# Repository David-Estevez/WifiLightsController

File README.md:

WifiLightsController
------------------------

Control a strip of several WS2812B with an ubicuous ESP8266 module

Author: [DEF](https://github.com/David-Estevez)

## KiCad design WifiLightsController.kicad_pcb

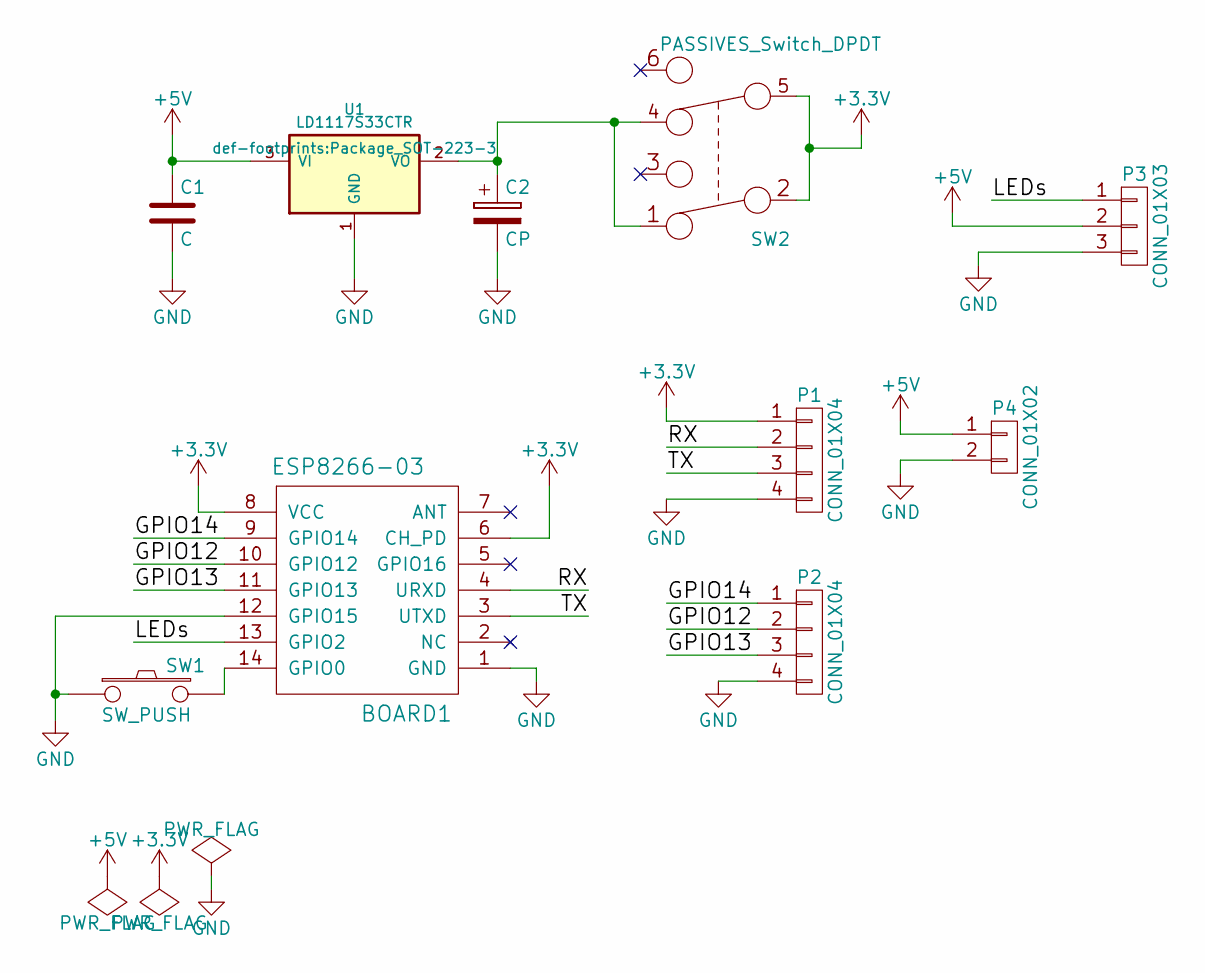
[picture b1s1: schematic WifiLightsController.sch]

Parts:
BOARD1: ESP8266-03; Board_ESP8266_03
C1: C; C_0805_HandSoldering
C2: CP; Package_1206_pol
P1: CONN_01X04; Pin_Header_Angled_1x04
P2: CONN_01X04; Pin_Header_Straight_1x04
P3: CONN_01X03; Pin_Header_Angled_1x03
P4: CONN_01X02; Pin_Header_Angled_1x02
SW1: SW_PUSH; Switches_Push_Switch_SMD_Seeedstudio_DHT-1163S
SW2: PASSIVES_Switch_DPDT; Switches_Switch_DPDT_SMD_Seeedstudio_311030005
U1: LD1117S33CTR; Package_SOT-223-3

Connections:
+3V3: BOARD1.6 (CH_PD), BOARD1.8 (VCC), P1.1, SW2.2, SW2.5
+5V: C1.1, P3.2, P4.1, U1.3 (VI)
/GPIO12: BOARD1.10 (GPIO12), P2.2
/GPIO13: BOARD1.11 (GPIO13), P2.3
/GPIO14: BOARD1.9 (GPIO14), P2.1
/LEDs: BOARD1.13 (GPIO2), P3.1
/RX: BOARD1.4 (URXD), P1.2
/TX: BOARD1.3 (UTXD), P1.3
GND: BOARD1.1 (GND), BOARD1.12 (GPIO15), C1.2, C2.2, P1.4, P2.4, P3.3, P4.2, SW1.1, U1.1 (GND)
unnamed: BOARD1.14 (GPIO0), SW1.2
unnamed: C2.1, SW2.1, SW2.4, U1.2 (VO)

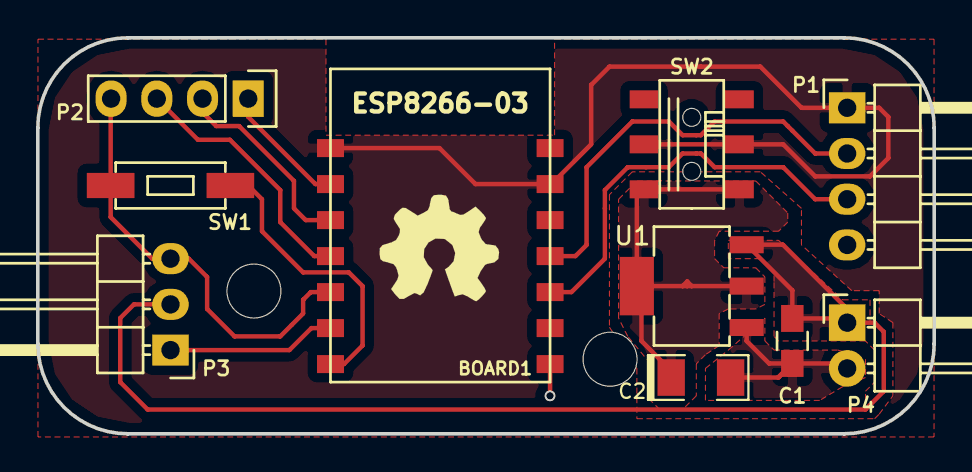
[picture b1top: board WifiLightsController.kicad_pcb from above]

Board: 2 copper layers, 49.8 x 22.0 mm, 12 parts (0 on the bottom side), 11 nets.

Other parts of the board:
Mechanical_drill_3mm, Mechanical_drill_3mm#2: Mechanical_Drill_3mm

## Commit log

2015-10-23 Routed board. Add silkcreen ids
2015-10-23 First prototype
2015-10-27 Generate GERBER files
2015-11-04 Add BOM file
2015-11-16 Move hardware files to independent folder
2015-11-16 Move fabrication files to hardware folder
2015-11-16 Add basic readme
2015-11-16 Correct typo on README
2015-11-16 Add datasheets for reference
2015-11-16 Add image to README
